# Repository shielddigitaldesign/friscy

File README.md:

# friscy
This repository will hold the fRISCy hardware design files

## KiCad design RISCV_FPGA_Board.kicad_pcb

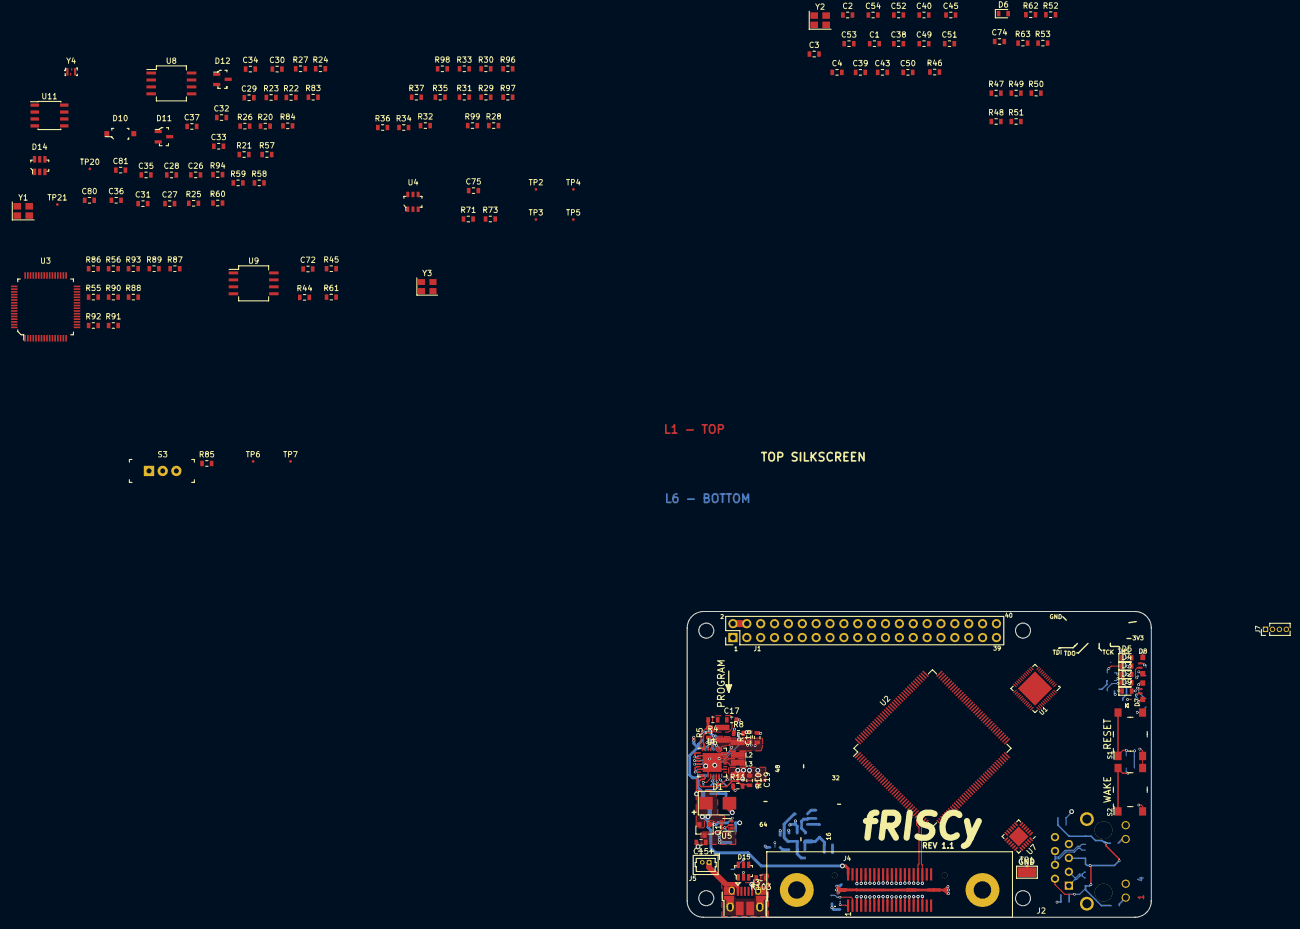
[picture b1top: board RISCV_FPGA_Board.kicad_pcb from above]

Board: 4 copper layers, 85.0 x 56.0 mm, 200 parts (0 on the bottom side), 203 nets.

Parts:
C1, C2, C29, C38, C43: 10uF; C_0603_1608Metric
C3, C15, C39: 1uF; C_0603_1608Metric
C4, C20, C21, C22, C27, C30, C31, C32, C33, C34, C35, C36, C37, C40, C45, C49, C50, C53, C54, C72, C74, C80: 0.1uF; C_0603_1608Metric
C14: 47uF; C_1210_3225Metric
C17, C18, C19, C23, C24, C25: 4.7uF; C_0603_1608Metric
C26, C28: 12pF; C_0603_1608Metric
C51, C52: 33pF; C_0603_1608Metric
C75: 1000pF; C_0603_1608Metric
C76, C78, C79: 22uF; C_0603_1608Metric
C77: 22pF; C_0603_1608Metric
C81: 10nF; C_0603_1608Metric
D1: SMBJ5.0A-E3/5B; D_SMB
D2, D3, D4, D5, D9: GREEN; LED_0603_1608Metric
D6: YELLOW; LED_0603_1608Metric
D7, D8: APFA3010LSEEZGKQBKC; LED_EDGE_MOUNT_RGB_KINGBRIGHT_APFA3010LSEEZGKQBKC
D10: 1N4148W-TP; SOD-123
D11, D12: BAT54; SOT-23-3
D14: USBLC6-4SC6; SOT23-6L
D15: USBLC6-2SC6; SOT23-6L
F1: MF-MSMF250/16X-2; R_1812_4532Metric
J1: PRPC020DFAN-RC; Pin_Header_Straight_2x20_Pitch2.54mm
J2: SI-60062-F
J3: 10103594-0001LF; USB_Micro-B_Amphenol_10103594-0001LF_Horizontal
J4: QSE-020-01-F-D-A-K; SYZYGY_Standard_Port
J5: 53047-0210; Molex_PicoBlade_53047-0210_02x1.25mm_Straight
J7: DNP, 4-pin, 0.05; Pin_Header_Straight_1x04_Pitch1.27mm
L1, L2, L3: 1uH; Neosid_Inductor_SM-NE29_SMD1008
L4: 2.2uH; Neosid_Inductor_SM-NE29_SMD1008
Q1: DMG2305UX-13; SOT-23
Q2, Q3: 2N7002DW; SOT-363_SC-70-6
R1, R12, R13, R14, R28, R44, R45, R52, R53, R61, R75, R81, R82, R86, R87, R88: 10k; R_0603_1608Metric
R2: 47.5k; R_0603_1608Metric
R3, R6, R9, R35, R38, R39, R40, R41, R96, R97, R98, R99: 49.9; R_0603_1608Metric
R4: 274k; R_0603_1608Metric
R5: 294k; R_0603_1608Metric
R7: 301k; R_0603_1608Metric
R8: 158k; R_0603_1608Metric
R10: 309k; R_0603_1608Metric
R11: 71.5k; R_0603_1608Metric
R15, R16, R17, R18, R54, R85: 604; R_0603_1608Metric
R19: 210k; R_0603_1608Metric
R20, R36, R37, R59: DNP; R_0603_1608Metric
R21, R71, R72, R83, R84: 100k; R_0603_1608Metric
R22: 100; R_0603_1608Metric
R23, R24, R25, R26, R27, R47, R48, R49, R50, R51, R68: 33; R_0603_1608Metric
R29: 1.5k; R_0603_1608Metric
R30, R31, R32, R33, R34, R57, R58, R79, R80, R89: 2.2k; R_0603_1608Metric
R42, R43: 274; R_0603_1608Metric
R46: 12.1k; R_0603_1608Metric
R55, R56: 12k; R_0603_1608Metric
R60, R73, R94, R103: 0; R_0603_1608Metric
R62, R63, R64, R65: 324; R_0603_1608Metric
R66, R67: 750; R_0603_1608Metric
R69: 750; R_0603
R70: 261; R_0603_1608Metric
R74: 37.4k; R_0603_1608Metric
R76: 44.2k; R_0603_1608Metric
R90, R91, R92, R93: 1k; R_0603_1608Metric
S1, S2: MJTP1138ATR; PTS645SM43SMTR92_LFS
S3: EG1218
TP1: 5015; TestPoint_Keystone_5015_Micro-Minature
TP2, TP3, TP4, TP5, TP6, TP7, TP20, TP21: TEST_1P; TestPoint_Round_20mil
U1: FE310-G000; QFN48_FE310
U2: iCE40-HX4K-TQ144; TQFP-144_20x20mm_P0.5mm
U3: FT4232HL-REEL; 64-LQFP_(10x10)
U4: SI3865DDV-T1-GE3; SOT-23-6
U5: BCM857BS,115; SOT-363_SC-70-6
U6: MIC23450; QFN-32-1EP_5x5mm_P0.5mm_EP3.45x3.45mm
U7: LAN8742AI-CZ; QFN-24-1EP_4x4mm_P0.5mm_EP2.6x2.6mm
U8: IS25LP128-JBLE; SO-8_5.3x6.2mm_P1.27mm
U9: MX25R6435FM2IH0; SO-8_5.3x6.2mm_P1.27mm
U11: 24AA256UIDT-I/SN; SOIC-8_3.9x4.9mm_P1.27mm
U13: AP3429AKTTR-G1; SOT-23-5
U14: MCP4716A0T-E/CH; SOT-23-6
Y1: 16MHz; Crystal_SMD_TXC_7M-4Pin_3.2x2.5mm
Y2: 25MHz; Crystal_SMD_TXC_7M-4Pin_3.2x2.5mm
Y3: ASEM1-100.000MHZ-LC-T; Oscillator_SMD_Abracon_ASE-4Pin_3.2x2.5mm
Y4: SIT1533AI-H4-DCC-32_768E; 1473-1239-1-ND

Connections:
+1V2: C1.1, C3.1, C4.1, C17.1, L1.2, R4.1, U6.31, U7.6
+1V8: C18.1, C29.1, C30.1, C32.1, C33.1, C80.1, D10.1, L2.2, R7.1, R22.2, R83.2, R84.2, U1.6, U1.19, U1.23, U1.30, U1.46, U6.4, Y4.4
+3V3: C19.1, C38.1, C39.1, C40.1, C49.1, C50.1, C53.1, C54.1, C74.1, D7.2, D8.2, D14.5, J1.1, J1.17, J2.2, J2.5, J4.40, L3.2, R10.1, R28.2, R29.2, R31.2, R33.2, R38.2, R39.2, R40.2, R41.2, R42.1, R43.1, R57.2, R58.2, R59.2, R71.1, R79.2, R80.2, R81.2, R82.2, S3.1, U2.89, U2.100, U2.123, U2.131, U4.4, U6.9, U7.1, U7.19, U11.8, U14.3, U14.6, Y3.1, Y3.4
+3V3_RISCV_IO: C27.1, C35.1, C36.1, C37.1, C75.1, R21.2, R70.2, U1.11, U1.12, U1.32, U1.47, U4.2, U4.3, U8.8
+5V: C14.1, C23.1, C24.1, C25.1, C76.1, D1.1, J1.2, J1.4, J4.2, Q1.2, R3.2, R6.2, R9.2, R12.2, R13.2, R14.2, R15.2, R16.2, R17.2, R18.2, R54.2, U5.4, U6.14, U6.27, U6.29, U6.30, U13.4
+VIO: C2.1, C72.1, C77.1, C78.1, C79.1, J4.39, L4.2, R44.2, R45.2, R52.2, R53.2, R61.2, R74.1, U2.6, U2.30, U2.46, U2.57, U7.9, U9.8
/E310_MCU/AON_LFCLK: U1.20, Y4.3
/E310_MCU/BRD_~RESET: D12.3, R51.1, R81.1, S1.1, S1.2, U2.73
/E310_MCU/I2C_SCL: J1.5, R58.1, TP20.1, U1.26, U2.141, U11.6
/E310_MCU/I2C_SDA: J1.3, R57.1, TP21.1, U1.25, U2.142, U11.5
/E310_MCU/MCU_GPIO_11: U1.35, U2.101
/E310_MCU/MCU_GPIO_12: U1.36, U2.102
/E310_MCU/MCU_GPIO_13: U1.37, U2.104
/E310_MCU/MCU_GPIO_18: U1.40, U2.105
/E310_MCU/MCU_GPIO_20: U1.42, U2.87
/E310_MCU/MCU_GPIO_23: U1.45, U2.88
/E310_MCU/MCU_LED_B: R64.1, U1.43
/E310_MCU/MCU_LED_G: R65.1, U1.41
/E310_MCU/MCU_LED_R: R66.1, U1.44
/E310_MCU/MCU_SPI_MISO: U1.29, U2.99
/E310_MCU/MCU_SPI_MOSI: R24.1, U2.98
/E310_MCU/MCU_SPI_SCK: R25.1, U2.94
/E310_MCU/MCU_SPI_~CS0: R23.1, U2.95
/E310_MCU/MCU_SPI_~CS2: R26.1, U2.96
/E310_MCU/MCU_SPI_~CS3: R27.1, U2.97
/E310_MCU/QSPI_CS0: R21.1, U1.5, U8.1
/E310_MCU/QSPI_DQ0: U1.4, U8.5
/E310_MCU/QSPI_DQ1: U1.3, U8.2
/E310_MCU/QSPI_DQ2: U1.2, U8.3
/E310_MCU/QSPI_DQ3: U1.1, U8.7
/E310_MCU/QSPI_SCK: U1.48, U8.6
/E310_MCU/RISCV_3V3_EN: U1.17, U4.5
/E310_MCU/RISCV_~WAKE_N: D11.3, R82.1, S2.1, S2.2, U2.74
/E310_MCU/UART0_RX: U1.38, U2.90
/E310_MCU/UART0_TX: U1.39, U2.91
/Ethernet/ETH_INT_RFCLKO: R35.1, U2.49
/Ethernet/ETH_MDC: U2.44, U7.13
/Ethernet/ETH_MDIO: U2.43, U7.12
/Ethernet/ETH_REF_CLK: C52.1, R37.2, U2.48, U7.5, Y2.1
/Ethernet/ETH_RSTN: R28.1, U2.47, U7.15
/Ethernet/ETH_RXD0: R98.1, U2.52
/Ethernet/ETH_RXD1: R99.1, U2.55
/Ethernet/ETH_RXERR: U2.56, U7.10
/Ethernet/ETH_RX_DV: U2.45, U7.11
/Ethernet/ETH_TXD0: R96.1, U2.60
/Ethernet/ETH_TXD1: R97.1, U2.61
/Ethernet/ETH_TX_EN: U2.42, U7.16
/Ethernet/RD_N: J2.6, R41.1, U7.23
/Ethernet/RD_P: J2.4, R40.1, U7.22
/Ethernet/TD_N: J2.3, R39.1, U7.21
/Ethernet/TD_P: J2.1, R38.1, U7.20
/FLASH/FPGA_MEM_MISO: U2.78, U9.2
/FLASH/FPGA_MEM_MOSI: U2.79, U9.5
/FLASH/FPGA_MEM_SCK: U2.81, U9.6
/FLASH/FPGA_MEM_~CE: R45.1, U2.80, U9.1
/FLASH/FPGA_MEM_~RESET: R61.1, U2.75, U9.7
/FLASH/FPGA_MEM_~WP: R44.1, U2.76, U9.3
/FPGA_Top/BCM4: J1.7, U2.130
/FPGA_Top/BCM5: J1.29, U2.119
/FPGA_Top/BCM6: J1.31, U2.118
/FPGA_Top/BCM7: J1.26, U2.138
/FPGA_Top/BCM8: J1.24, U2.139
/FPGA_Top/BCM9: J1.21, U2.121
/FPGA_Top/BCM10: J1.19, U2.122
/FPGA_Top/BCM11: J1.23, U2.120
/FPGA_Top/BCM12: J1.32, U2.137
/FPGA_Top/BCM13: J1.33, U2.117
/FPGA_Top/BCM16: J1.36, U2.136
/FPGA_Top/BCM17: J1.11, U2.128
/FPGA_Top/BCM18: J1.12, U2.107
/FPGA_Top/BCM19: J1.35, U2.116
/FPGA_Top/BCM20: J1.38, U2.135
/FPGA_Top/BCM21: J1.40, U2.134
/FPGA_Top/BCM22: J1.15, U2.124
/FPGA_Top/BCM23: J1.16, U2.106
/FPGA_Top/BCM24: J1.18, U2.112
/FPGA_Top/BCM25: J1.22, U2.110
/FPGA_Top/BCM26: J1.37, U2.115
/FPGA_Top/BCM27: J1.13, U2.125
/FPGA_Top/FTDI_UART_RX: R90.1, U2.85
/FPGA_Top/FTDI_UART_TX: R91.2, U2.93
/FPGA_Top/ID_SC: J1.28, U2.113
/FPGA_Top/ID_SD: J1.27, U2.114
/FPGA_Top/SYSCLK_100M: R68.1, U2.129
/FPGA_Top/SZ_C2P_CLK_N: J4.36, U2.34
/FPGA_Top/SZ_C2P_CLK_P: J4.34, U2.33
/FPGA_Top/SZ_D0_N: J4.7, U2.4
/FPGA_Top/SZ_D0_P: J4.5, U2.3
/FPGA_Top/SZ_D1_N: J4.8, U2.2
/FPGA_Top/SZ_D1_P: J4.6, U2.1
/FPGA_Top/SZ_D2_N: J4.11, U2.10
/FPGA_Top/SZ_D2_P: J4.9, U2.9
/FPGA_Top/SZ_D3_N: J4.12, U2.8
/FPGA_Top/SZ_D3_P: J4.10, U2.7
/FPGA_Top/SZ_D4_N: J4.15, U2.16
/FPGA_Top/SZ_D4_P: J4.13, U2.15
/FPGA_Top/SZ_D5_N: J4.16, U2.12
/FPGA_Top/SZ_D5_P: J4.14, U2.11
/FPGA_Top/SZ_D6_N: J4.19, U2.22
/FPGA_Top/SZ_D6_P: J4.17, U2.21
/FPGA_Top/SZ_D7_N: J4.20, U2.18
/FPGA_Top/SZ_D7_P: J4.18, U2.17
/FPGA_Top/SZ_P2C_CLK_N: J4.35, U2.19
/FPGA_Top/SZ_P2C_CLK_P: J4.33, U2.20
/FPGA_Top/SZ_S16: J4.21, U2.24
/FPGA_Top/SZ_S17: J4.22, U2.23
/FPGA_Top/SZ_S18: J4.23, U2.26
/FPGA_Top/SZ_S19: J4.24, U2.25
/FPGA_Top/SZ_S20: J4.25, U2.29
/FPGA_Top/SZ_S21: J4.26, U2.28
/FPGA_Top/SZ_S22: J4.27, U2.32
/FPGA_Top/SZ_S23: J4.28, U2.31
/FPGA_Top/SZ_S24: J4.29, U2.38
/FPGA_Top/SZ_S25: J4.30, U2.37
/FPGA_Top/SZ_S26: J4.31, U2.41
/FPGA_Top/SZ_S27: J4.32, U2.39
/FPGA_Top/SZ_SCL: J4.1, R79.1, U2.83, U14.5
/FPGA_Top/SZ_SDA: J4.3, R80.1, U2.84, U14.4
/FPGA_Top/SZ_VIO_EN: R72.1, U2.82, U13.1
/FPGA_Top/UART_H_RX: J1.10, U2.143
/FPGA_Top/UART_H_TX: J1.8, U2.144
/FT2232/+3V3_FTDI: R55.2, R85.2, R86.1, R87.2, R88.1, S3.2, S3.3
/FT2232/JTAG_TCK: D14.1, J7.1, R47.1, TP5.1, U1.13
/FT2232/JTAG_TDI: D14.3, J7.4, R48.1, R92.2, TP2.1, U1.16
/FT2232/JTAG_TDO: D14.6, J7.2, R49.1, TP4.1, U1.14
/FT2232/JTAG_TMS: D14.4, J7.3, R50.1, R93.2, TP3.1, U1.15
/FT2232/USB_D_N: D15.1, D15.6, J3.2
/FT2232/USB_D_P: D15.3, D15.4, J3.3
/Power/+V_INPUT: D15.5, F1.2, J3.1, J5.1
/Power/PG_1V0: Q2.2, R12.1, U6.1, U6.3
/Power/PG_1V8: Q2.5, R13.1, U6.6, U6.8
/Power/PG_3V3: Q3.2, R14.1, U6.12
/SYZYGY_Conn/SZ_R_GA: J4.4, R19.2
GND: C1.2, C2.2, C3.2, C4.2, C14.2, C15.2, C17.2, C18.2, C19.2, C20.2, C21.2, C22.2, C23.2, C24.2, C25.2, C26.2, C27.2, C28.2, C29.2, C30.2, C32.2, C33.2, C35.2, C36.2, C37.2, C38.2, C39.2, C40.2, C49.2, C50.2, C51.2, C52.2, C53.2, C54.2, C72.2, C74.2, C76.2, C78.2, C79.2, C80.2, C81.2, D1.2, D5.1, D9.1, D14.2, D15.2, J1.6, J1.9, J1.14, J1.20, J1.25, J1.30, J1.34, J1.39, J2.8, J2.13, J3.5, J4.41, J4.42, J4.43, J4.44, J5.2, Q2.1, Q2.4, Q3.1, Q3.4, R1.2, R2.2, R5.1, R8.1, R11.1, R19.1, R30.1, R32.1, R34.1, R46.1, R56.2, R60.1, R72.2, R73.1, R75.2, R91.1, R92.1, R93.1, R94.1, R103.2, S1.3, S1.4, S2.3, S2.4, TP1.1, U1.49, U6.2, U6.7, U6.11, U6.18, U6.22, U6.24, U6.33, U7.25, U8.4, U9.4, U11.2, U11.3, U11.4, U13.2, U14.2, Y1.2, Y1.4, Y2.2, Y2.4, Y3.2, Y4.2
unnamed: C15.1, F1.1, Q1.3, U5.1
unnamed: C20.1, R3.1, U6.28
unnamed: C21.1, R6.1, U6.15
unnamed: C22.1, R9.1, U6.13
unnamed: C26.1, R20.2, U1.9, Y1.1
unnamed: C28.1, R20.1, U1.10, Y1.3
unnamed: C31.2, U1.8
unnamed: C51.1, R36.2, R37.1, Y2.3
unnamed: C75.2, R71.2, U4.6
unnamed: C77.2, R74.2, R75.1, R76.1, U13.5
unnamed: C81.1, D10.2, D12.1, R83.1, U1.24
unnamed: D2.1, Q2.6
unnamed: D2.2, R15.1
unnamed: D3.1, Q2.3
unnamed: D3.2, R16.1
unnamed: D4.1, Q3.6
unnamed: D4.2, R17.1
unnamed: D5.2, R18.1
unnamed: D6.1, Q3.3
unnamed: D6.2, R54.1
unnamed: D7.1, R66.2
unnamed: D7.3, R65.2
unnamed: D7.4, R64.2
unnamed: D8.1, R67.2, R69.2
unnamed: D8.3, R63.2
unnamed: D8.4, R62.2
unnamed: D9.2, R70.1
unnamed: D11.1, R84.1, U1.18
unnamed: J2.9, R42.2
unnamed: J2.10, U7.3
unnamed: J2.11, U7.2
unnamed: J2.12, R43.2
unnamed: J3.6, R103.1
unnamed: L1.1, U6.26
unnamed: L2.1, U6.23
unnamed: L3.1, U6.21
unnamed: L4.1, U13.3
unnamed: Q1.1, R2.1, U5.3
unnamed: Q3.5, R53.1, TP7.1, U2.65
unnamed: R1.1, U5.2, U5.5, U5.6
unnamed: R4.2, R5.2, U6.32
unnamed: R7.2, R8.2, U6.5
unnamed: R10.2, R11.2, U6.10
unnamed: R22.1, U1.7
unnamed: R23.2, U1.27
unnamed: R24.2, U1.28
unnamed: R25.2, U1.31
unnamed: R26.2, U1.33
unnamed: R27.2, U1.34
unnamed: R35.2, U7.14
unnamed: R36.1, U7.4
unnamed: R46.2, U7.24
unnamed: R52.1, TP6.1, U2.66
unnamed: R59.1, R60.2, U11.1
unnamed: R62.1, U2.62
unnamed: R63.1, U2.63
unnamed: R67.1, U2.64
unnamed: R68.2, Y3.3
unnamed: R73.2, U4.1
unnamed: R76.2, U14.1
unnamed: R87.1, R89.2
unnamed: R94.2, U1.21
unnamed: R96.2, U7.17
unnamed: R97.2, U7.18
unnamed: R98.2, U7.8
unnamed: R99.2, U7.7
unnamed: U2.5, U2.13, U2.14, U2.59, U2.69, U2.86, U2.103, U2.132, U2.140
unnamed: U2.27, U2.40, U2.92, U2.111
unnamed: U2.35, U2.36, U2.50, U2.51, U2.58, U2.77, U2.133

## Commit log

2020-02-15 Never actually added my design files...
    This was intended to be an exciting FPGA + RISC-V board in the Raspberry Pi form factor. I nearly completed the design with a Xilinx FPGA, but decided to switch to a Lattice iCE40 due to the new open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
